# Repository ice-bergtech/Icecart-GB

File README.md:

# Icecart-GB

Another ROM Cartridge for the Gameboy.
Purpose is to fit the form factor of a gameboy cartridge and act as a ROM cartridge while also providing an arduino-like interface.
Emulates the functionality of an official cart, with the different bank controllers implemented in software.

[Schematic](GB-ICECART-GB-Alpha/schematic/GB-ICECART-GB.pdf)

It should also have functionality similar to an arduino, where you can interface with it through GPIO and audio in/out.
It should be as low-power as possible, since it will run off the gameboy battery.
It should support an sd card for storage while powered off.

Requirements:

* STM32-type processor
  * low power
  * Enough pins for cart and GPIO (32+16)
  * rtc
* External mic + speaker 3.8mm jacks
* dac connection to gameboy cartridge audio line for input
* usb C for programming / updating
* 2x8 or 2x6 GPIO
* microsd card slot for storage
* 32Mbit serial ram
* Respond to gameboy cartridge read/write (1MHz ??? Not sure) 
  * 4Mihz for gameboy: [gekkio notes](https://gekkio.fi/files/gb-docs/gbctr.pdf) appendix C
  * 8Mihz for gameboy color?
  * More timing information: https://dhole.github.io/post/gameboy_cartridge_emu_1/
* gameboy dmg/color cartridge footprint
  * https://github.com/Gekkio/gb-hardware/tree/main/GB-BRK-CART
* FreeRTOS

Examples:

* emeryth-hacks: https://emeryth.net/stm32-game-boy-cartridge/
* gekkio: https://github.com/Gekkio/gb-hardware#gb-live32

References:

[Old Memory bank controllers](https://mgba-emu.github.io/gbdoc/#mbc)
[TPP1 mapper](https://github.com/aaaaaa123456789/tpp1)

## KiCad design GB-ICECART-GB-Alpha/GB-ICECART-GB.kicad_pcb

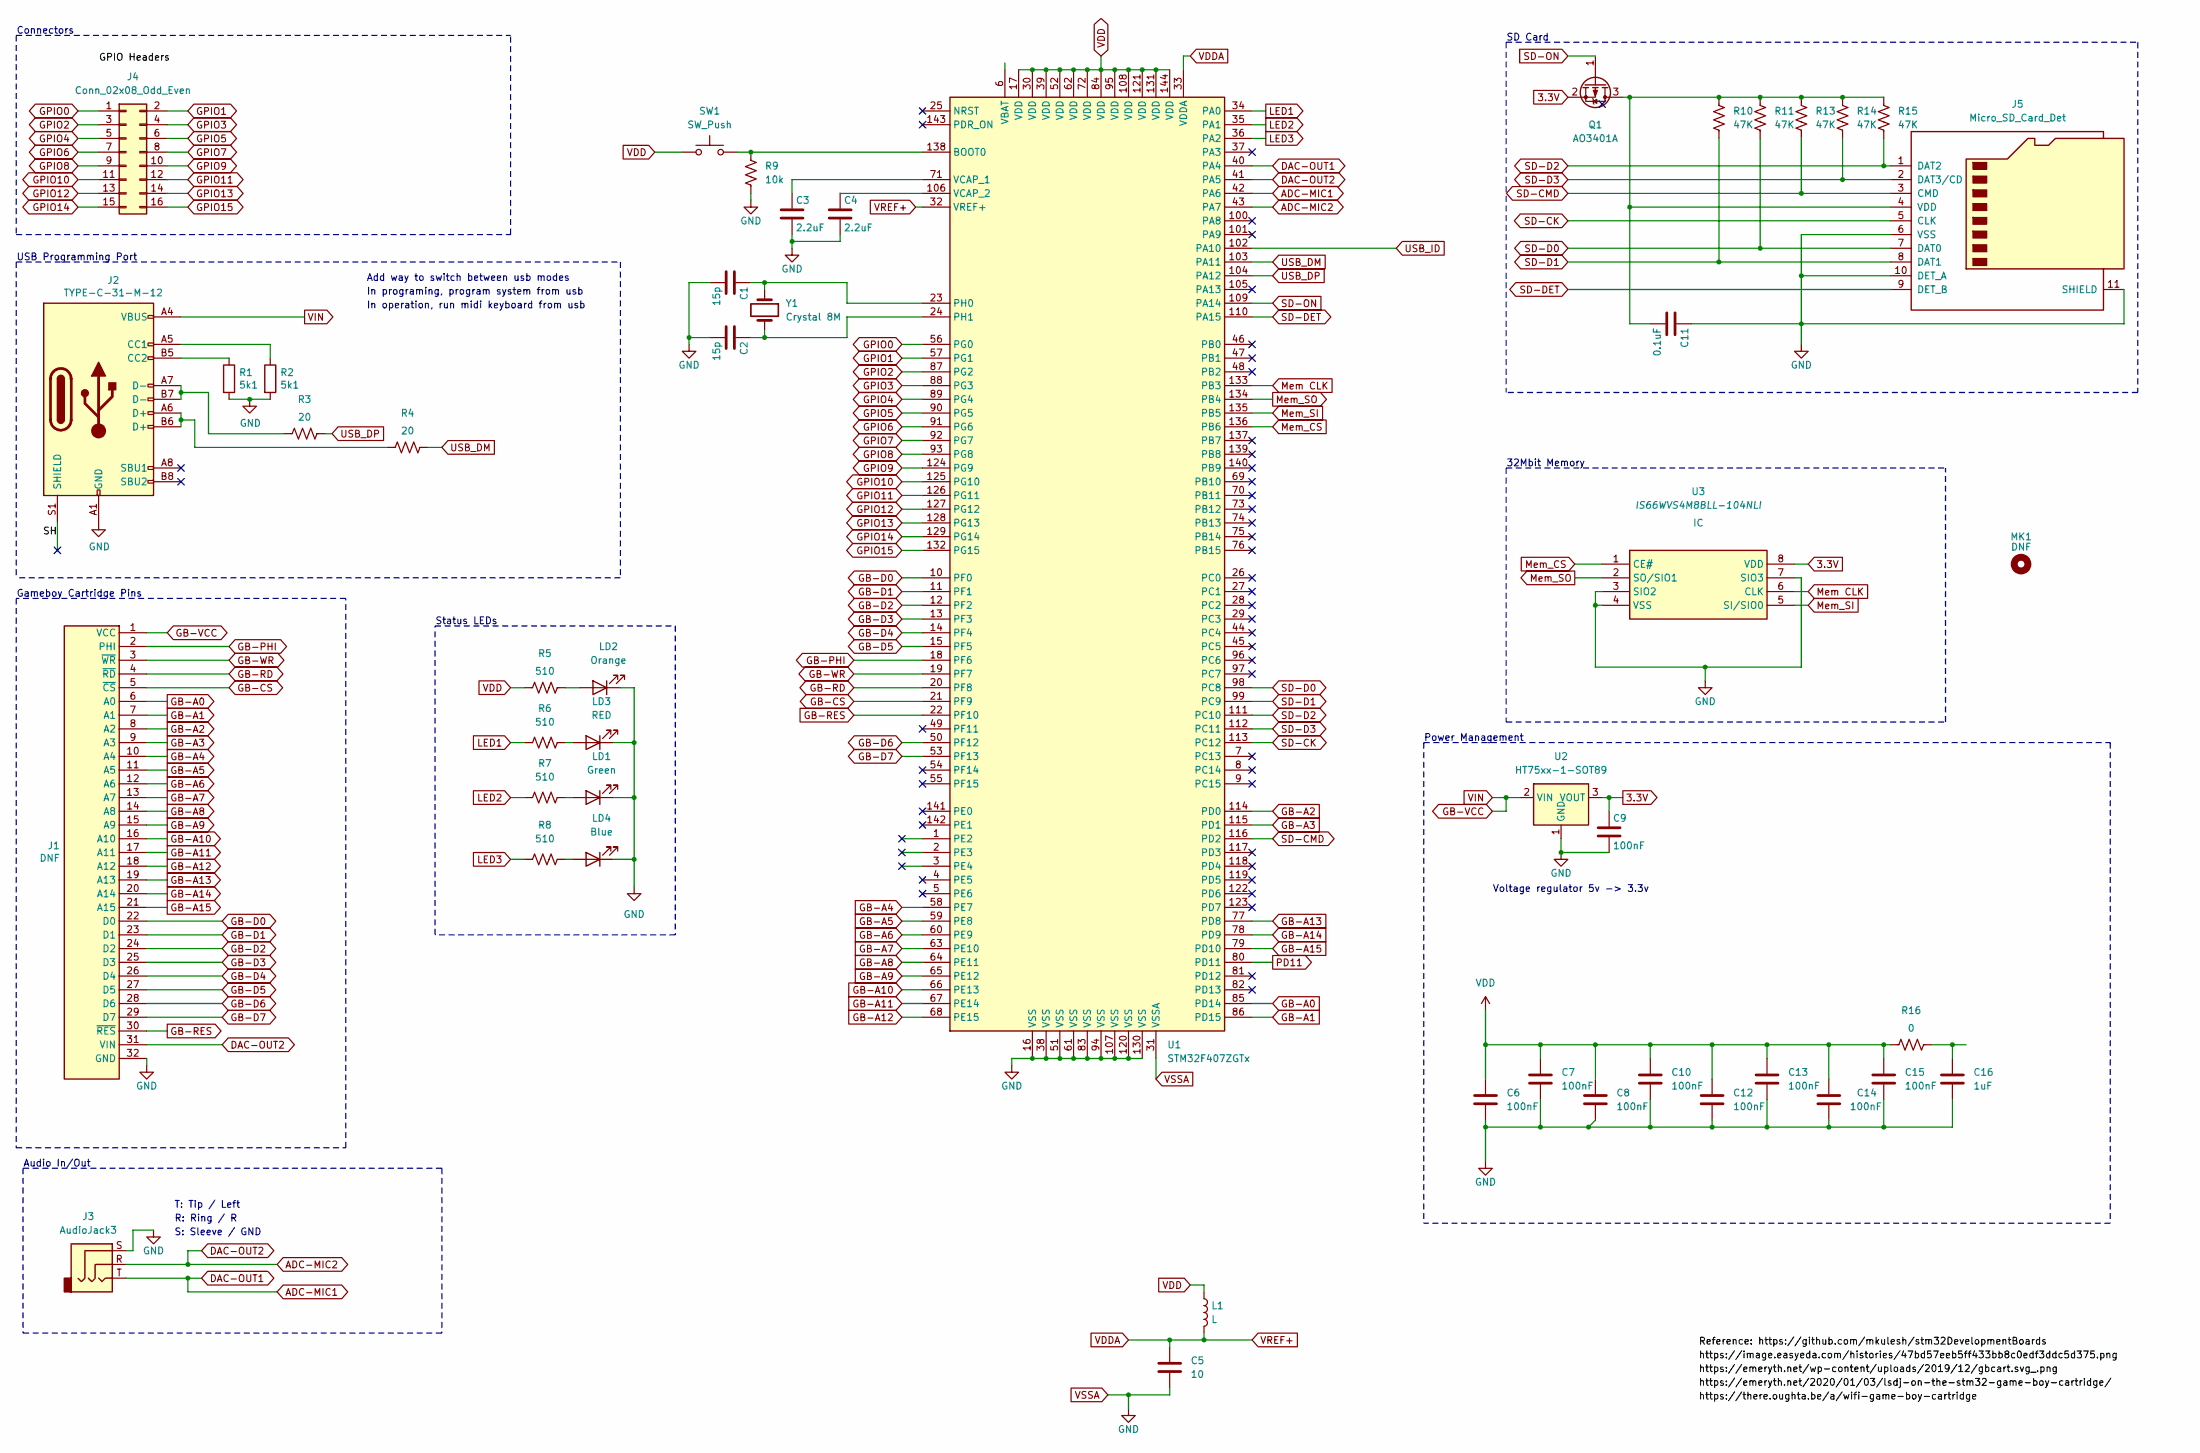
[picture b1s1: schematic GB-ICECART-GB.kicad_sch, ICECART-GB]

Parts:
C1, C2: 15p; C_0603_1608Metric; Rating 16V X5R; MPN 06035C104KAT4A
C3, C4: 2.2uF; C_0603_1608Metric; Rating 16V X5R; MPN 06035C104KAT4A
C5: 10; C_0603_1608Metric
C6, C7, C8, C10, C12, C13, C14, C15: 100nF; C_0603_1608Metric
C9: 100nF; C_0603_1608Metric; Rating 16V X5R; MPN 06035C104KAT4A
C11: 0.1uF; C_0603_1608Metric; Rating 16V X5R; MPN 06035C104KAT4A
C16: 1uF; C_0603_1608Metric
J1: DNF; GameBoy_Cartridge_1x32_P1.50mm_Edge
J2: TYPE-C-31-M-12; USB_C_Receptacle_HRO_TYPE-C-31-M-12
J3: AudioJack3; Jack_3.5mm_CUI_SJ1-3523N_Horizontal
J4: Conn_02x08_Odd_Even; IDC-Header_2x08_P2.54mm_Vertical_SMD
J5: Micro_SD_Card_Det; microSD_HC_Hirose_DM3AT-SF-PEJM5
L1: L; L_6.3x6.3_H3
LD1: Green; LED_0603_1608Metric
LD2: Orange; LED_0603_1608Metric
LD3: RED; LED_0603_1608Metric
LD4: Blue; LED_0603_1608Metric
MK1: DNF; MountingHole_7.2mm
Q1: AO3401A; SOT-23
R1, R2: 5k1; R_0603_1608Metric
R3, R4: 20; R_0603_1608Metric
R5, R6, R7, R8: 510; R_0603_1608Metric
R9: 10k; R_0603_1608Metric
R10, R11, R13, R14, R15: 47K; R_0603_1608Metric
R16: 0; R_0603_1608Metric
SW1: SW_Push; SW_SPST_B3U-1000P
U1: STM32F407ZGTx; LQFP-144_20x20mm_P0.5mm
U2: HT75xx-1-SOT89; SOT-89-3
U3: IS66WVS4M8BLL-104NLI; SOIC127P600X175-8N; Mouser Part Number 870-ISS4M8BLL-104NLI
Y1: Crystal 8M; Crystal_SMD_TXC_7M-4Pin_3.2x2.5mm

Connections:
3.3V: C9.1, Q1.2 (S), U2.3 (VOUT), U3.8 (VDD)
/SH: J2.S1 (SHIELD)
/SH_0: J2.S1 (SHIELD)
/SH_1: J2.S1 (SHIELD)
/SH_2: J2.S1 (SHIELD)
ADC-MIC1: J3.T, U1.40 (PA4), U1.42 (PA6)
ADC-MIC2: J1.31 (VIN), J3.R, U1.41 (PA5), U1.43 (PA7)
GB-A0: J1.6 (A0), U1.85 (PD14)
GB-A1: J1.7 (A1), U1.86 (PD15)
GB-A2: J1.8 (A2), U1.114 (PD0)
GB-A3: J1.9 (A3), U1.115 (PD1)
GB-A4: J1.10 (A4), U1.58 (PE7)
GB-A5: J1.11 (A5), U1.59 (PE8)
GB-A6: J1.12 (A6), U1.60 (PE9)
GB-A7: J1.13 (A7), U1.63 (PE10)
GB-A8: J1.14 (A8), U1.64 (PE11)
GB-A9: J1.15 (A9), U1.65 (PE12)
GB-A10: J1.16 (A10), U1.66 (PE13)
GB-A11: J1.17 (A11), U1.67 (PE14)
GB-A12: J1.18 (A12), U1.68 (PE15)
GB-A13: J1.19 (A13), U1.77 (PD8)
GB-A14: J1.20 (A14), U1.78 (PD9)
GB-A15: J1.21 (A15), U1.79 (PD10)
GB-CS: J1.5 (~CS), U1.21 (PF9)
GB-D0: J1.22 (D0), U1.10 (PF0)
GB-D1: J1.23 (D1), U1.11 (PF1)
GB-D2: J1.24 (D2), U1.12 (PF2)
GB-D3: J1.25 (D3), U1.13 (PF3)
GB-D4: J1.26 (D4), U1.14 (PF4)
GB-D5: J1.27 (D5), U1.15 (PF5)
GB-D6: J1.28 (D6), U1.50 (PF12)
GB-D7: J1.29 (D7), U1.53 (PF13)
GB-PHI: J1.2 (PHI), U1.18 (PF6)
GB-RD: J1.4 (~RD), U1.20 (PF8)
GB-RES: J1.30 (~RES), U1.22 (PF10)
GB-VCC: J1.1 (VCC), J2.A4 (VBUS), J2.A9 (VBUS), J2.B4 (VBUS), J2.B9 (VBUS), U2.2 (VIN)
GB-WR: J1.3 (~WR), U1.19 (PF7)
GPIO0: J4.1, U1.56 (PG0)
GPIO1: J4.2, U1.57 (PG1)
GPIO2: J4.3, U1.87 (PG2)
GPIO3: J4.4, U1.88 (PG3)
GPIO4: J4.5, U1.89 (PG4)
GPIO5: J4.6, U1.90 (PG5)
GPIO6: J4.7, U1.91 (PG6)
GPIO7: J4.8, U1.92 (PG7)
GPIO8: J4.9, U1.93 (PG8)
GPIO9: J4.10, U1.124 (PG9)
GPIO10: J4.11, U1.125 (PG10)
GPIO11: J4.12, U1.126 (PG11)
GPIO12: J4.13, U1.127 (PG12)
GPIO13: J4.14, U1.128 (PG13)
GPIO14: J4.15, U1.129 (PG14)
GPIO15: J4.16, U1.132 (PG15)
LED1: R6.1, U1.34 (PA0)
LED2: R7.1, U1.35 (PA1)
LED3: R8.1, U1.36 (PA2)
Mem CLK: U1.133 (PB3), U3.6 (CLK)
Mem_CS: U1.136 (PB6), U3.1 (CE#)
Mem_SI: U1.135 (PB5), U3.5 (SI/SIO0)
Mem_SO: U1.134 (PB4), U3.2 (SO/SIO1)
unnamed: C16.1, R16.2
unnamed: J2.A5 (CC1), R2.1
unnamed: J2.B5 (CC2), R1.1
unnamed: J2.A6 (D+), J2.B6 (D+), R4.1
unnamed: J2.A7 (D-), J2.B7 (D-), R3.1
unnamed: C11.2, J5.4 (VDD), Q1.3 (D), R10.1, R11.1, R13.1, R14.1, R15.1
unnamed: LD1.2 (A), R7.2
unnamed: LD2.2 (A), R5.2
unnamed: LD3.2 (A), R6.2
unnamed: LD4.2 (A), R8.2
unnamed: R9.1, SW1.2, U1.138 (BOOT0)
unnamed: C1.1, U1.23 (PH0), Y1.1
unnamed: C2.1, U1.24 (PH1), Y1.2
unnamed: C3.1, U1.71 (VCAP_1)
unnamed: C4.1, U1.106 (VCAP_2)
PD11: U1.80 (PD11)
SD-CK: J5.5 (CLK), U1.113 (PC12)
SD-CMD: J5.3 (CMD), R13.2, U1.116 (PD2)
SD-D0: J5.7 (DAT0), R11.2, U1.98 (PC8)
SD-D1: J5.8 (DAT1), R10.2, U1.99 (PC9)
SD-D2: J5.1 (DAT2), R15.2, U1.111 (PC10)
SD-D3: J5.2 (DAT3/CD), R14.2, U1.112 (PC11)
SD-DET: J5.9 (DET_B), U1.110 (PA15)
SD-ON: Q1.1 (G), U1.109 (PA14)
USB_DM: R4.2, U1.103 (PA11)
USB_DP: R3.2, U1.104 (PA12)
USB_ID: U1.102 (PA10)
VDD: C6.1, C7.1, C8.1, C10.1, C12.1, C13.1, C14.1, C15.1, L1.1, R5.1, R16.1, SW1.1, U1.17 (VDD), U1.30 (VDD), U1.39 (VDD), U1.52 (VDD), U1.62 (VDD), U1.72 (VDD), U1.84 (VDD), U1.95 (VDD), U1.108 (VDD), U1.121 (VDD), U1.131 (VDD), U1.144 (VDD)
VDDA: C5.1, L1.2, U1.32 (VREF+), U1.33 (VDDA)
VSSA: C1.2, C2.2, C3.2, C4.2, C5.2, C6.2, C7.2, C8.2, C9.2, C10.2, C11.1, C12.2, C13.2, C14.2, C15.2, C16.2, J1.32 (GND), J2.A1 (GND), J2.A12 (GND), J2.B1 (GND), J2.B12 (GND), J3.S, J5.6 (VSS), J5.10 (DET_A), J5.11 (SHIELD), LD1.1 (K), LD2.1 (K), LD3.1 (K), LD4.1 (K), R1.2, R2.2, R9.2, U1.16 (VSS), U1.31 (VSSA), U1.38 (VSS), U1.51 (VSS), U1.61 (VSS), U1.83 (VSS), U1.94 (VSS), U1.107 (VSS), U1.120 (VSS), U1.130 (VSS), U2.1 (GND), U3.3 (SIO2), U3.4 (VSS), U3.7 (SIO3)

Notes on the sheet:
USB Programming Port
SD Card
Audio In/Out
R: Ring / R
Connectors
S: Sleeve / GND
Add way to switch between usb modes
32Mbit Memory
T: Tip / Left
Status LEDs
In operation, run midi keyboard from usb
In programing, program system from usb
Power Management
Gameboy Cartridge Pins
Voltage regulator 5v -> 3.3v

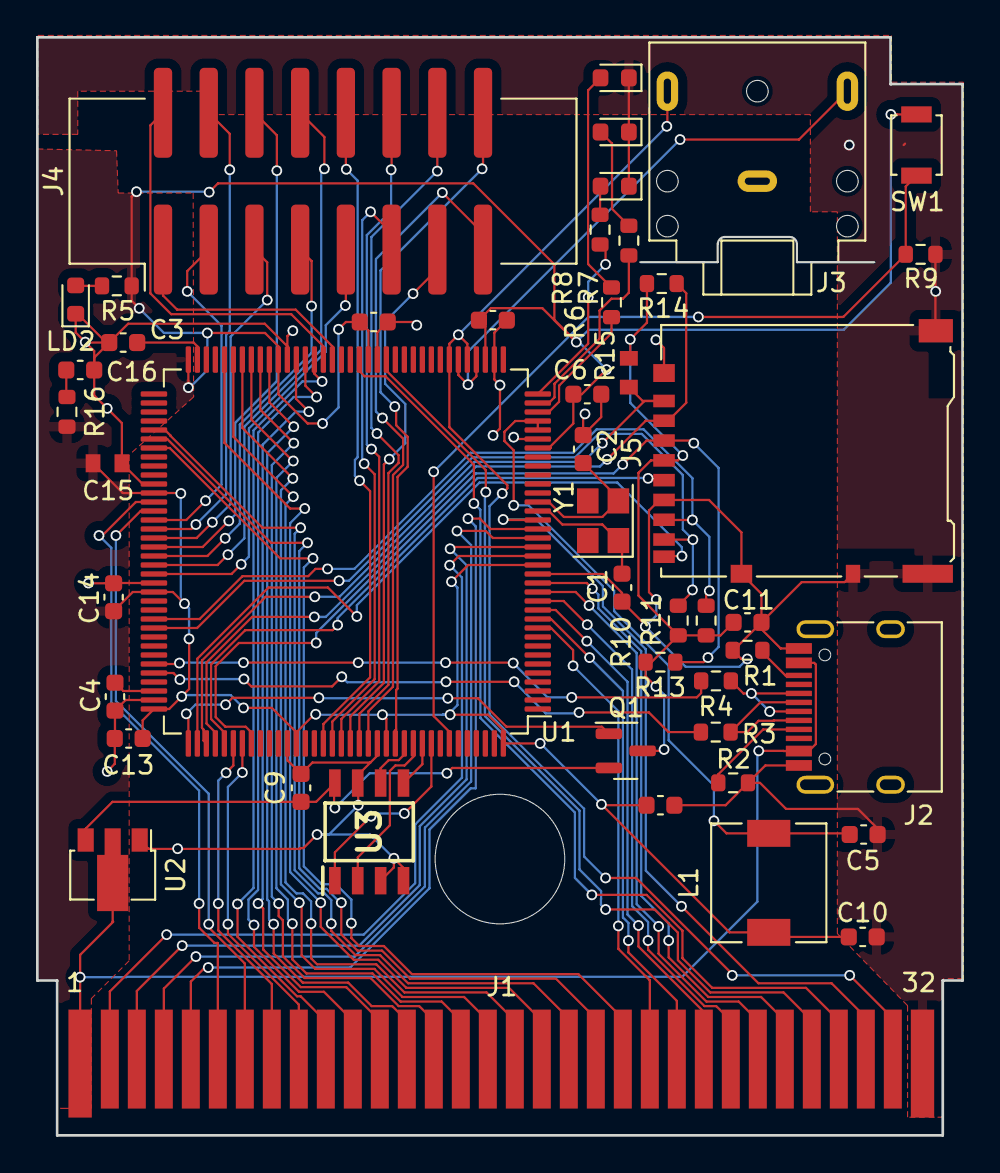
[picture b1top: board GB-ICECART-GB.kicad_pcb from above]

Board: 2 copper layers, 51.4 x 61.0 mm, 48 parts (0 on the bottom side), 84 nets.

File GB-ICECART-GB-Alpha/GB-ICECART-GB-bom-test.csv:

"Reference","Value","Datasheet","Footprint","Qty","DNP"
"C1,C2","15p","-- mixed values --","Capacitor_SMD:C_0603_1608Metric","2",""
"C3,C4","2.2uF","","Capacitor_SMD:C_0603_1608Metric","2",""
"C5","10","~","Capacitor_SMD:C_0603_1608Metric","1",""
"C6,C7,C8,C9,C10,C12,C13,C14,C15","100nF","-- mixed values --","Capacitor_SMD:C_0603_1608Metric","9",""
"C11","0.1uF","","Capacitor_SMD:C_0603_1608Metric","1",""
"C16","1uF","~","Capacitor_SMD:C_0603_1608Metric","1",""
"J1,MK1,MK2","DNF","","-- mixed values --","3",""
"J2","TYPE-C-31-M-12","https://www.usb.org/sites/default/files/documents/usb_type-c.zip","Connector_USB:USB_C_Receptacle_HRO_TYPE-C-31-M-12","1",""
"J3","AudioJack3","~","Connector_Audio:Jack_3.5mm_CUI_SJ1-3523N_Horizontal","1",""
"J4","Conn_02x08_Odd_Even","~","Connector_IDC:IDC-Header_2x08_P2.54mm_Vertical_SMD","1",""
"J5","Micro_SD_Card_Det","https://www.hirose.com/product/en/download_file/key_name/DM3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","Connector_Card:microSD_HC_Hirose_DM3AT-SF-PEJM5","1",""
"L1","L","~","Inductor_SMD:L_6.3x6.3_H3","1",""
"LD1","Green","~","LED_SMD:LED_0603_1608Metric","1",""
"LD2","Orange","~","LED_SMD:LED_0603_1608Metric","1",""
"LD3","RED","~","LED_SMD:LED_0603_1608Metric","1",""
"LD4","Blue","~","LED_SMD:LED_0603_1608Metric","1",""
"Q1","AO3401A","http://www.aosmd.com/pdfs/datasheet/AO3401A.pdf","Package_TO_SOT_SMD:SOT-23","1",""
"R1,R2","5k1","~","Resistor_SMD:R_0603_1608Metric","2",""
"R3,R4","20","~","Resistor_SMD:R_0603_1608Metric","2",""
"R5,R6,R7,R8","510","~","Resistor_SMD:R_0603_1608Metric","4",""
"R9","10k","~","Resistor_SMD:R_0603_1608Metric","1",""
"R10,R11,R13,R14,R15","47K","~","Resistor_SMD:R_0603_1608Metric","5",""
"R16","0","~","Resistor_SMD:R_0603_1608Metric","1",""
"SW1","SW_Push","~","Button_Switch_SMD:SW_SPST_B3U-1000P","1",""
"U1","STM32F407ZGTx","http://www.st.com/st-web-ui/static/active/en/resource/techni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","Package_QFP:LQFP-144_20x20mm_P0.5mm","1",""
"U2","HT75xx-1-SOT89","https://www.holtek.com/documents/10179/116711/HT75xx-1v250.pdf","Package_TO_SOT_SMD:SOT-89-3","1",""
"U3","IS66WVS4M8BLL-104NLI","","IS66WVS4M8BLL:SOIC127P600X175-8N","1",""
"Y1","Crystal 8M","~","Crystal:Crystal_SMD_TXC_7M-4Pin_3.2x2.5mm","1",""

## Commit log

2023-11-28 Initial Prototyping and planning
2023-12-01 Add model of design
2023-12-06 Update schematic and hook more up
2023-12-08 Add schematic and pcb design images
2024-04-22 Add new version
2024-06-25 Preliminary routing and BOM
2024-06-25 Organizing exports
2024-06-25 Add informal webpage
2024-06-25 website edits
2024-06-25 Add git link
2024-06-25 Add JLC PCB export
2025-05-19 setup pico gb
